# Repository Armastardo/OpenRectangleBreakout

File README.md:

# Open Rectangle Breakout
RaspberryPi Pico-powered breakout board for a stickless controller

Design files are available in this repository. Production files for JLCPCB in the releases page. Currently untested.

## Table of contents
* [Features](#features)
* [Usage](#usage)
* [To-do](#to-do)
* [Acknowledgements](#acknowledgements)

## Features
- USB-C to GCC and USB-C to N64 cable compatible with integrated port or with a [Model-U](https://github.com/Crane1195/Model-U).
- Can use non detachable OEM/Third party gamecube cables.
- Uses [HayBox](https://github.com/JonnyHaystack/HayBox) and [Pico Rectangle](https://github.com/JulienBernard3383279/pico-rectangle) default pinout. Labeled accordingly with some extra pins broken out if you want to expand functionality (WASD layout, add another LED, etc).

## Usage
1. Order via JLCPCB using the production files in the releases page.
	- Solder screw terminals if prefered.
2. Connect them to the PC and the first time it'll show up as a mass storage device.
3. Drop your prefered firmware in uf2 format and once it disconnects it should be good to go.
	- If you connect while pressing the BOOT button, it'll show again as a mass storage device so you can update the firmware or replace it.

## To-do:
- Use it in a build! Please share pics if you do so. My discord username is Quark#0009

### Made using the Open Rectangle Template
OpenRectangleTemplate project] - https://github.com/Armastardo/OpenRectangleTemplate

This was just a proof of concept to see how easy it is to use the template. It's good! But I still need to work on both projects to get them to where I want.

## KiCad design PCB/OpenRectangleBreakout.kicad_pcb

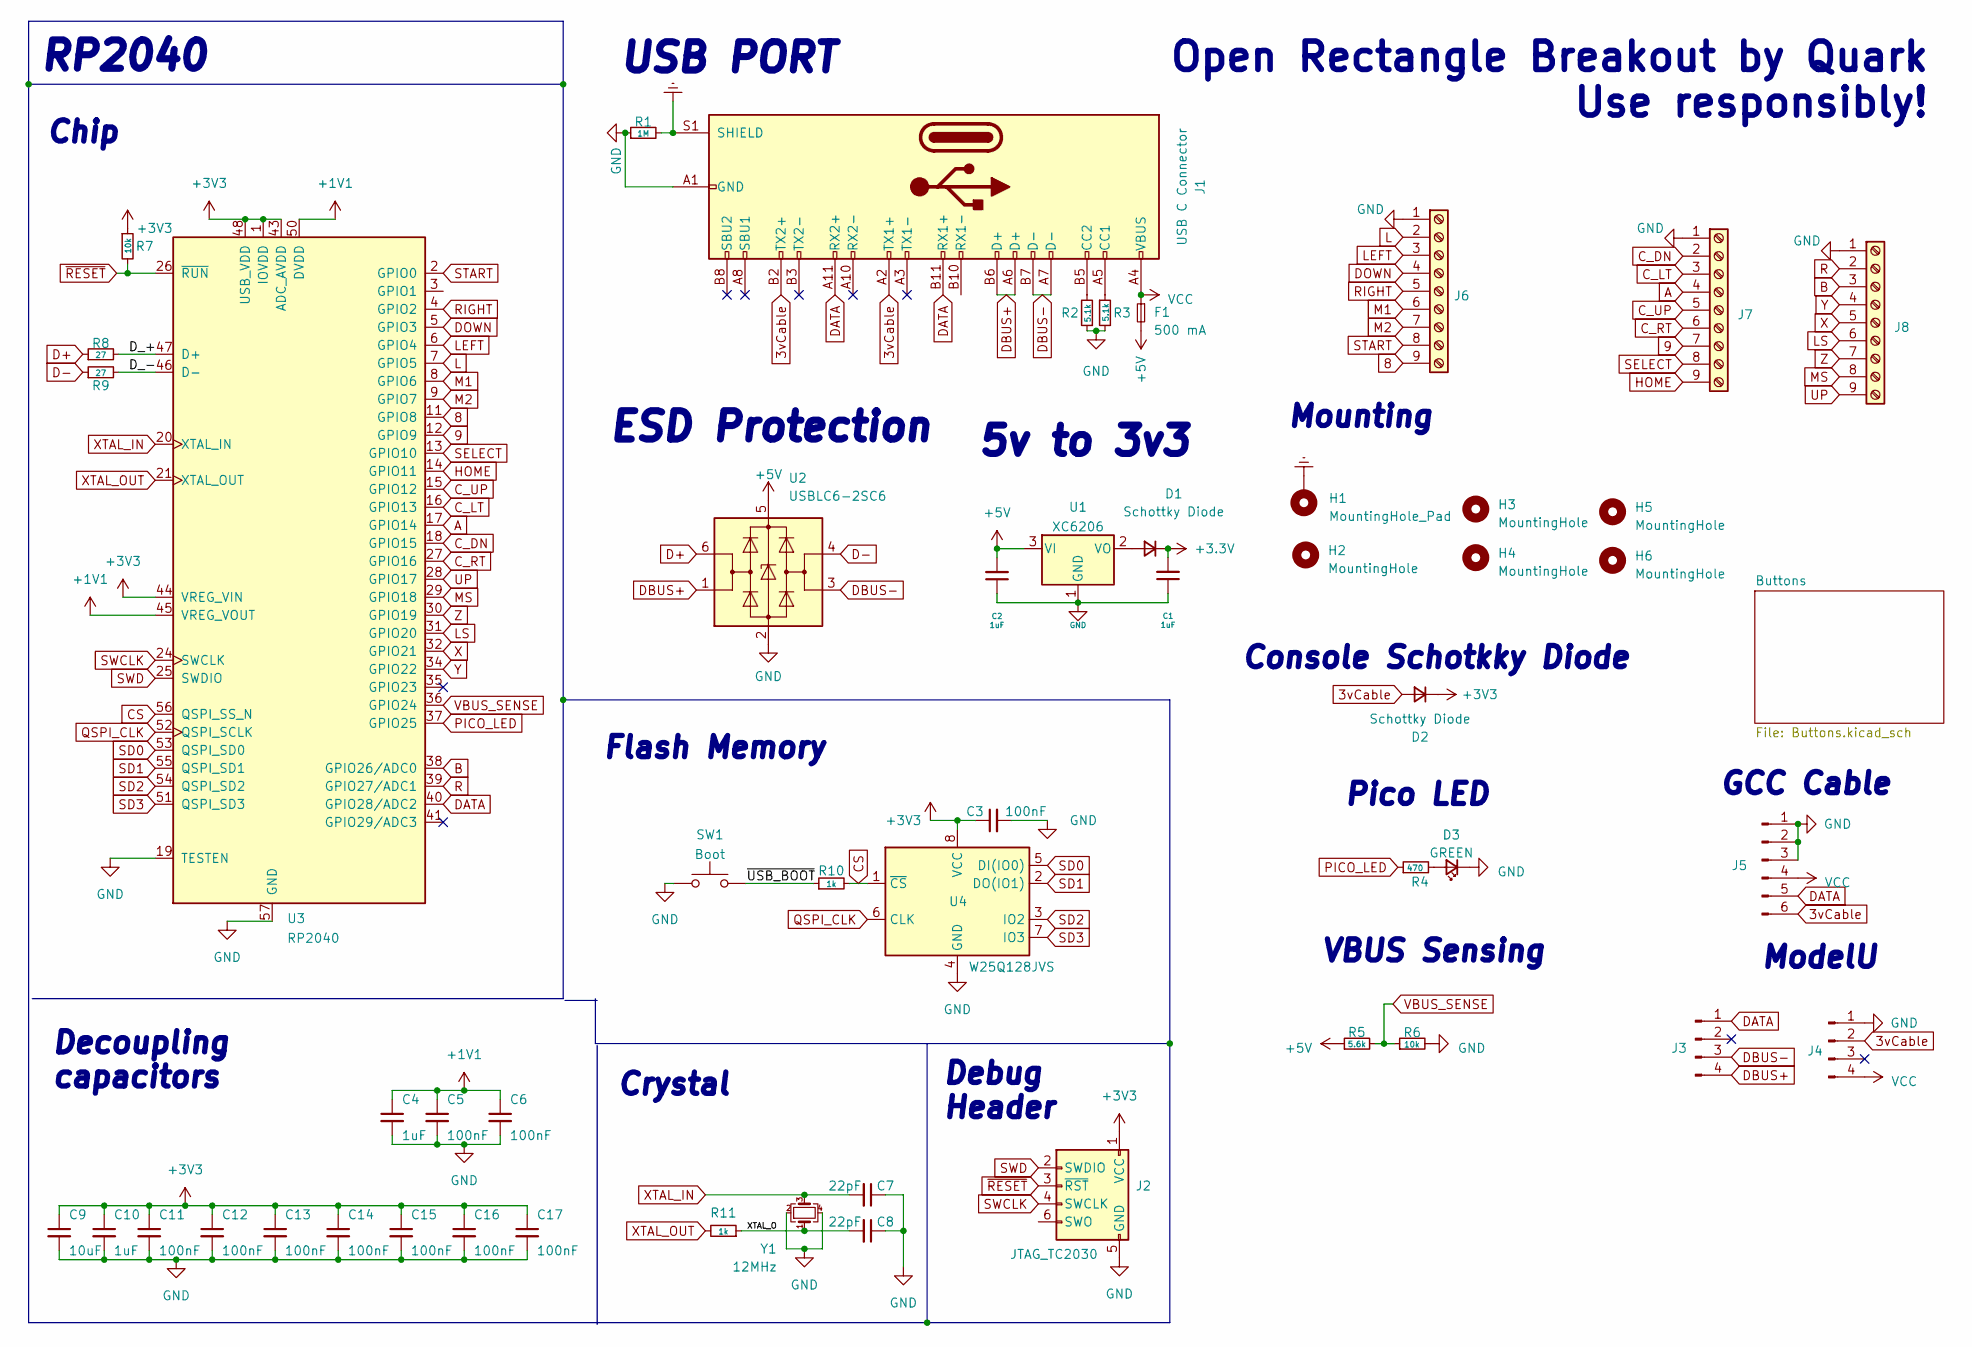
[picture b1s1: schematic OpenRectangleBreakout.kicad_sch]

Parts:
C1, C2, C4, C10: 1uF; C_0402_1005Metric; LCSC C52923
C3, C5, C6, C11, C12, C13, C14, C15, C16, C17: 100nF; C_0402_1005Metric; LCSC C1525
C7, C8: 22pF; C_0402_1005Metric; LCSC C1555
C9: 10uF; C_0402_1005Metric; LCSC C15525
D1, D2: Schottky Diode; D_SOD-123; LCSC C130880
D3: GREEN; LED_0805_2012Metric; LCSC C2297
F1: 500 mA; Fuse_1206_3216Metric
H1: MountingHole_Pad; MountingHole_2.2mm_M2_ISO14580_Pad
H2, H3, H4, H5, H6: MountingHole; MountingHole_2.1mm
J1: USB C Connector; TYPE-C_24P_QCHT; LCSC C456013
J2: JTAG_TC2030; CON_TC2030_outlined
J3, J4: Conn_01x04_Pin; PinHeader_1x04_P2.54mm_Vertical
J5: GCC Cable; PinHeader_1x06_P2.00mm_Vertical
J6, J7, J8: Screw_Terminal_01x09; PinHeader_1x09_P2.54mm_Vertical
R1: 1M; R_0603_1608Metric; LCSC C25190
R2, R3: 5.1k; R_0402_1005Metric; LCSC C25744
R4: 470; R_0402_1005Metric; LCSC C25117
R5: 5.6k; R_0402_1005Metric
R6: 10k; R_0402_1005Metric
R7: 10k; R_0402_1005Metric; LCSC C25744
R8, R9: 27; R_0603_1608Metric; LCSC C25190
R10, R11: 1k; R_0402_1005Metric; LCSC C11702
SW1: Boot; SW_SPST_SKQG_WithStem; LCSC C5156480
U1: XC6206; SOT-23; LCSC C5446
U2: USBLC6-2SC6; SOT-23-6
U3: RP2040; RP2040-QFN-56; LCSC C2040
U4: W25Q128JVS; SOIC-8_5.23x5.23mm_P1.27mm; LCSC C97521
Y1: 12MHz; Crystal_SMD_3225-4Pin_3.2x2.5mm; LCSC C9002

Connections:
3vCable: D2.2 (A), J1.A2 (TX1+), J1.B2 (TX2+), J4.2, J5.6
8: J6.9, U3.11 (GPIO8)
9: J7.7, U3.12 (GPIO9)
+1V1: C4.1, C5.1, C6.1, U3.23 (DVDD), U3.45 (VREG_VOUT), U3.50 (DVDD)
+5V: C2.2, F1.2, R5.1, U1.3 (VI), U2.5 (VBUS)
/D_+: R8.2, U3.47 (D+)
/D_-: R9.2, U3.46 (D-)
/XTAL_O: C8.2, R11.1, Y1.1
/~USB_BOOT: R10.1, SW1.2
A: J7.4, U3.17 (GPIO14)
B: J8.3, U3.38 (GPIO26/ADC0)
CS: R10.2, U3.56 (QSPI_SS_N), U4.1 (~CS)
C_DN: J7.2, U3.18 (GPIO15)
C_LT: J7.3, U3.16 (GPIO13)
C_RT: J7.6, U3.27 (GPIO16)
C_UP: J7.5, U3.15 (GPIO12)
D+: R8.1, U2.6 (I/O1)
D-: R9.1, U2.4 (I/O2)
DATA: J1.A11 (RX2+), J1.B11 (RX1+), J3.1, J5.5, U3.40 (GPIO28/ADC2)
DBUS+: J1.A6 (D+), J1.B6 (D+), J3.4, U2.1 (I/O1)
DBUS-: J1.A7 (D-), J1.B7 (D-), J3.3, U2.3 (I/O2)
DOWN: J6.4, U3.5 (GPIO3)
Earth: H1.1, J1.S1 (SHIELD), R1.2
GND: C1.1, C2.1, C3.2, C4.2, C5.2, C6.2, C7.1, C8.1, C9.2, C10.2, C11.2, C12.2, C13.2, C14.2, C15.2, C16.2, C17.2, D3.1 (K), J1.A1 (GND), J1.A12 (GND), J1.B1 (GND), J1.B12 (GND), J2.5 (GND), J4.1, J5.1, J5.2, J5.3, J6.1, J7.1, J8.1, R1.1, R2.1, R3.2, R6.2, SW1.1, U1.1 (GND), U2.2 (GND), U3.19 (TESTEN), U3.57 (GND), U4.4 (GND), Y1.2, Y1.4
HOME: J7.9, U3.14 (GPIO11)
L: J6.2, U3.7 (GPIO5)
LEFT: J6.3, U3.6 (GPIO4)
LS: J8.6, U3.31 (GPIO20)
M1: J6.6, U3.8 (GPIO6)
M2: J6.7, U3.9 (GPIO7)
MS: J8.8, U3.29 (GPIO18)
unnamed: D1.2 (A), U1.2 (VO)
unnamed: D3.2 (A), R4.2
unnamed: J1.A5 (CC1), R3.1
unnamed: J1.B5 (CC2), R2.2
PICO_LED: R4.1, U3.37 (GPIO25)
QSPI_CLK: U3.52 (QSPI_SCLK), U4.6 (CLK)
R: J8.2, U3.39 (GPIO27/ADC1)
RIGHT: J6.5, U3.4 (GPIO2)
SD0: U3.53 (QSPI_SD0), U4.5 (DI(IO0))
SD1: U3.55 (QSPI_SD1), U4.2 (DO(IO1))
SD2: U3.54 (QSPI_SD2), U4.3 (IO2)
SD3: U3.51 (QSPI_SD3), U4.7 (IO3)
SELECT: J7.8, U3.13 (GPIO10)
START: J6.8, U3.2 (GPIO0)
SWCLK: J2.4 (SWCLK), U3.24 (SWCLK)
SWD: J2.2 (SWDIO), U3.25 (SWDIO)
UP: J8.9, U3.28 (GPIO17)
VBUS_SENSE: R5.2, R6.1, U3.36 (GPIO24)
VCC: F1.1, J1.A4 (VBUS), J1.A9 (VBUS), J1.B4 (VBUS), J1.B9 (VBUS), J4.4, J5.4
X: J8.5, U3.32 (GPIO21)
XTAL_IN: C7.2, U3.20 (XTAL_IN), Y1.3
XTAL_OUT: R11.2, U3.21 (XTAL_OUT)
Y: J8.4, U3.34 (GPIO22)
Z: J8.7, U3.30 (GPIO19)
~RESET: J2.3 (~RST), R7.2, U3.26 (~RUN)

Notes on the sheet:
Console Schotkky Diode
Crystal
USB PORT
Flash Memory
ModelU
Pico LED
Mounting
Open Rectangle Breakout by Quark Use responsibly!
RP2040
GCC Cable
Debug Header
VBUS Sensing
Chip
5v to 3v3
ESD Protection
Decoupling capacitors

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
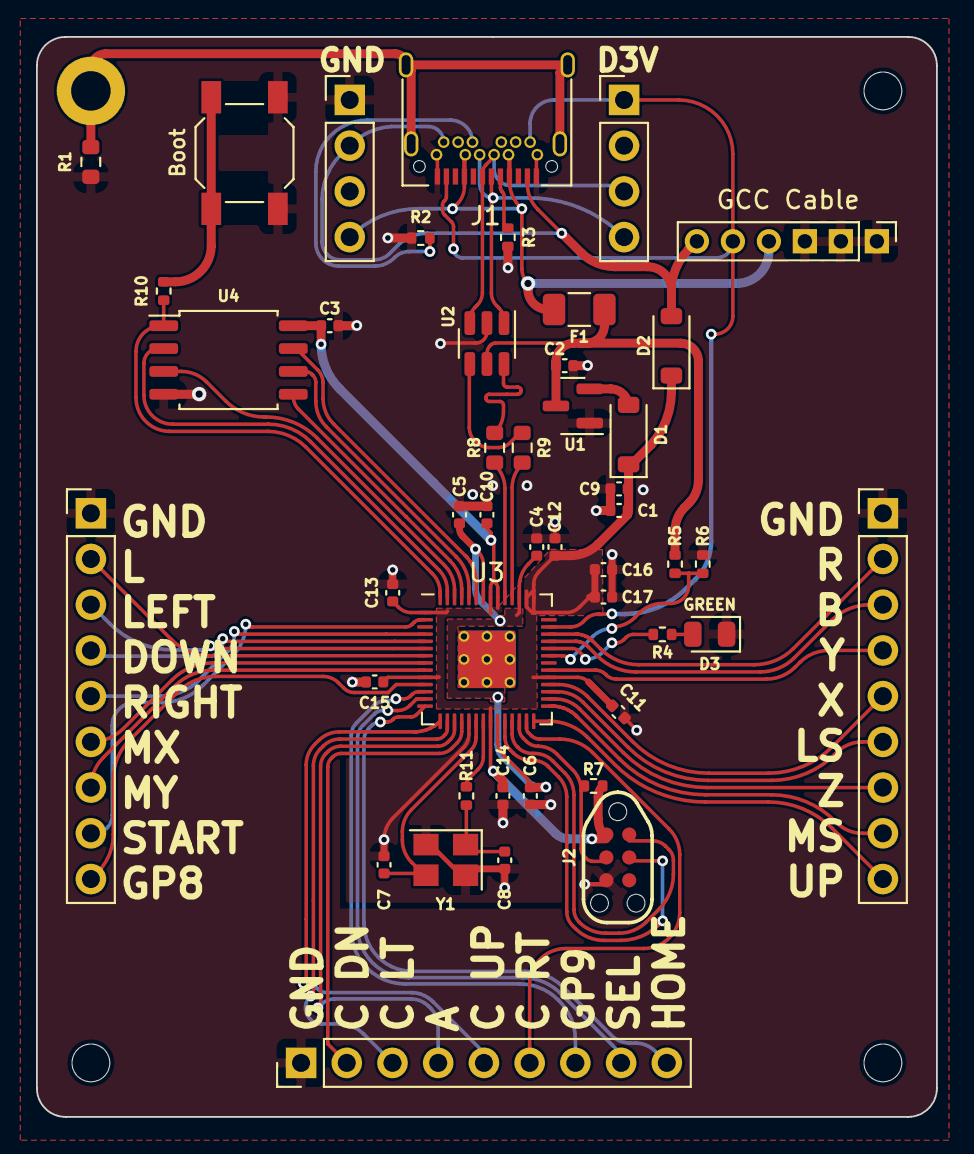
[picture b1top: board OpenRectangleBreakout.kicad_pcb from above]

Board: 2 copper layers, 50.0 x 60.0 mm, 50 parts (0 on the bottom side), 57 nets.

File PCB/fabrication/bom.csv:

Designator,Footprint,Quantity,Value,LCSC Part #
C1,402,1,1uF,C52923
C10,402,1,1uF,C52923
C11,402,1,100nF,C1525
C12,402,1,100nF,C1525
C13,402,1,100nF,C1525
C14,402,1,100nF,C1525
C15,402,1,100nF,C1525
C16,402,1,100nF,C1525
C17,402,1,100nF,C1525
C2,402,1,1uF,C52923
C3,402,1,100nF,C1525
C4,402,1,1uF,C52923
C5,402,1,100nF,C1525
C6,402,1,100nF,C1525
C7,402,1,22pF,C1555
C8,402,1,22pF,C1555
C9,402,1,10uF,C15525
"D1, D2",D_SOD-123,2,Schottky Diode,C8598
D3,805,1,GREEN,C2297
F1,1206,1,500 mA,C70076
J1,TYPE-C_24P_QCHT,1,USB C Connector,C456013
R1,603,1,1M,C25190
R10,402,1,1k,C11702
R11,402,1,1k,C11702
R2,402,1,5.1k,C25744
R3,402,1,5.1k,C25744
R4,402,1,470,C25117
R5,402,1,5.6k,C25908
R6,402,1,10k,C25744
R7,402,1,10k,C25744
R8,603,1,27,C25190
R9,603,1,27,C25190
U1,SOT-23,1,XC6206,C5446
U2,SOT-23-6,1,USBLC6-2SC6,C323793
U3,RP2040-QFN-56,1,RP2040,C2040
U4,SOIC-8_5.23x5.23mm_P1.27mm,1,W25Q128JVS,C97521
Y1,Crystal_SMD_3225-4Pin_3.2x2.5mm,1,12MHz,C9002
SW1,Button_Switch_SMD:SW_SPST_SKQG_WithStem,1,Boot,C202424

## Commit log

2023-03-05 First version
2023-03-05 Adjusted styling and broken links
2023-03-05 Fixed the POS file
2023-03-20 Fixed START button to the correct pin
